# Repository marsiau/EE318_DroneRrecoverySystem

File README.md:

# EE318_DroneRrecoverySystem
Drone recovery system project for EE318

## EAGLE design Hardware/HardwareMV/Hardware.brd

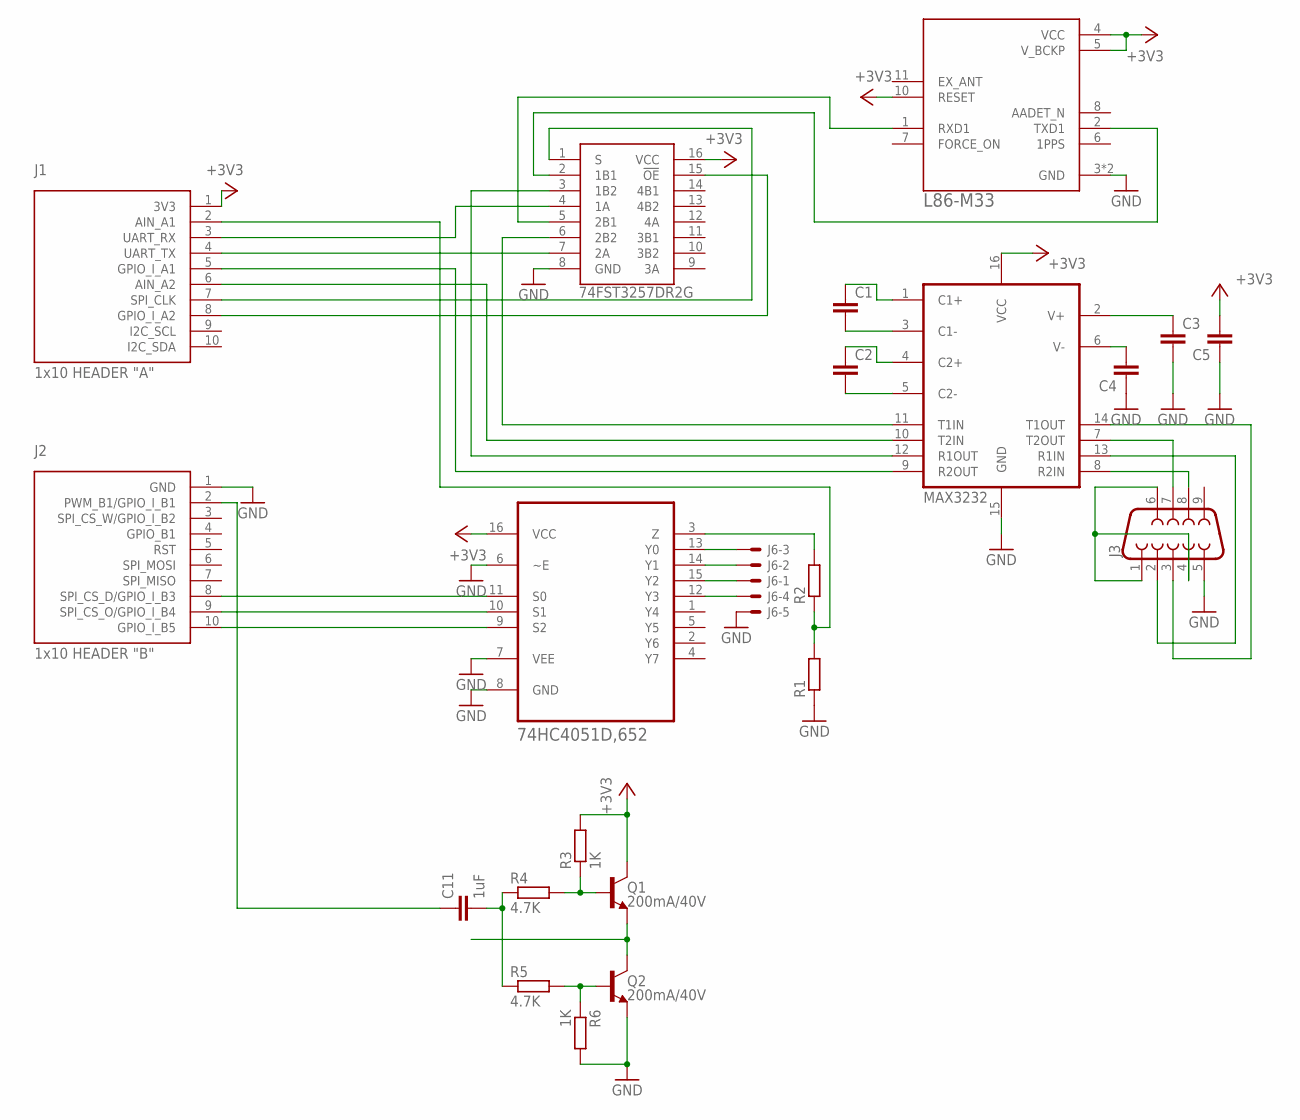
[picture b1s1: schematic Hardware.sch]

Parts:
C1, C2, C3, C4, C5: C-EUC0805K; C0805K
C11: 1uF; C025-024X044
IC1: 74FST3257DR2G; SOIC127P600X175-16N
J1: 1x10 HEADER "A"; 1X10
J2: 1x10 HEADER "B"; 1X10
J3: DB9MALE; DB9_MALE
J6: 22-27-2051-05; 6410-05
Q1, Q2: 200mA/40V; TO-92
R1, R2: R-EU_0207/7; 0207/7
R3, R6: 1K; 0207/2V
R4, R5: 4.7K; 0207/2V
U1: MAX3232; SO16
U2: L86-M33; SON254P1840X1840X40-12N
U4: 74HC4051D,652; SOIC127P600X175-16N

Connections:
+3V3: C5.2, IC1.16 (VCC), J1.1 (3V3), Q1.3 (C), R3.2, U1.16 (VCC), U2.4 (VCC), U2.5 (V_BCKP), U2.10 (RESET), U4.16 (VCC)
GND: C3.2, C4.1, C5.1, IC1.8 (GND), J2.1 (GND), J3.5, J6.5, Q2.1 (E), R1.1, R6.2, U1.15 (GND), U2.3 (GND), U2.12 (GND), U4.6 (~E), U4.7 (VEE), U4.8 (GND)
unnamed: C1.1, U1.1 (C1+)
unnamed: C1.2, U1.3 (C1-)
unnamed: IC1.4 (1A), J1.3 (UART_RX)
unnamed: C2.1, U1.4 (C2+)
unnamed: IC1.7 (2A), J1.4 (UART_TX)
unnamed: C3.1, U1.2 (V+)
unnamed: C4.2, U1.6 (V-)
unnamed: IC1.2 (1B1), U2.2 (TXD1)
unnamed: C2.2, U1.5 (C2-)
unnamed: IC1.5 (2B1), U2.1 (RXD1)
unnamed: IC1.3 (1B2), U1.12 (R1OUT)
unnamed: J3.1, J3.4, J3.6
unnamed: J3.2, U1.13 (R1IN)
unnamed: J3.3, U1.14 (T1OUT)
unnamed: J3.8, U1.8 (R2IN)
unnamed: J3.7, U1.7 (T2OUT)
unnamed: IC1.6 (2B2), U1.11 (T1IN)
unnamed: IC1.1 (S), J1.7 (SPI_CLK)
unnamed: IC1.15 (!OE), J1.8 (GPIO_I_A2)
unnamed: J6.3, U4.13 (Y0)
unnamed: J1.6 (AIN_A2), U1.10 (T2IN)
unnamed: J6.2, U4.14 (Y1)
unnamed: J6.1, U4.15 (Y2)
unnamed: J6.4, U4.12 (Y3)
unnamed: R2.2, U4.3 (Z)
unnamed: J1.5 (GPIO_I_A1), U1.9 (R2OUT)
unnamed: J1.2 (AIN_A1), R1.2, R2.1
unnamed: J2.8 (SPI_CS_D/GPIO_I_B3), U4.11 (S0)
unnamed: J2.9 (SPI_CS_O/GPIO_I_B4), U4.10 (S1)
unnamed: J2.10 (GPIO_I_B5), U4.9 (S2)
unnamed: C11.2, R4.1, R5.1
unnamed: C11.1, J2.2 (PWM_B1/GPIO_I_B1)
unnamed: Q2.2 (B), R5.2, R6.1
unnamed: Q1.2 (B), R3.1, R4.2
unnamed: Q1.1 (E), Q2.3 (C)

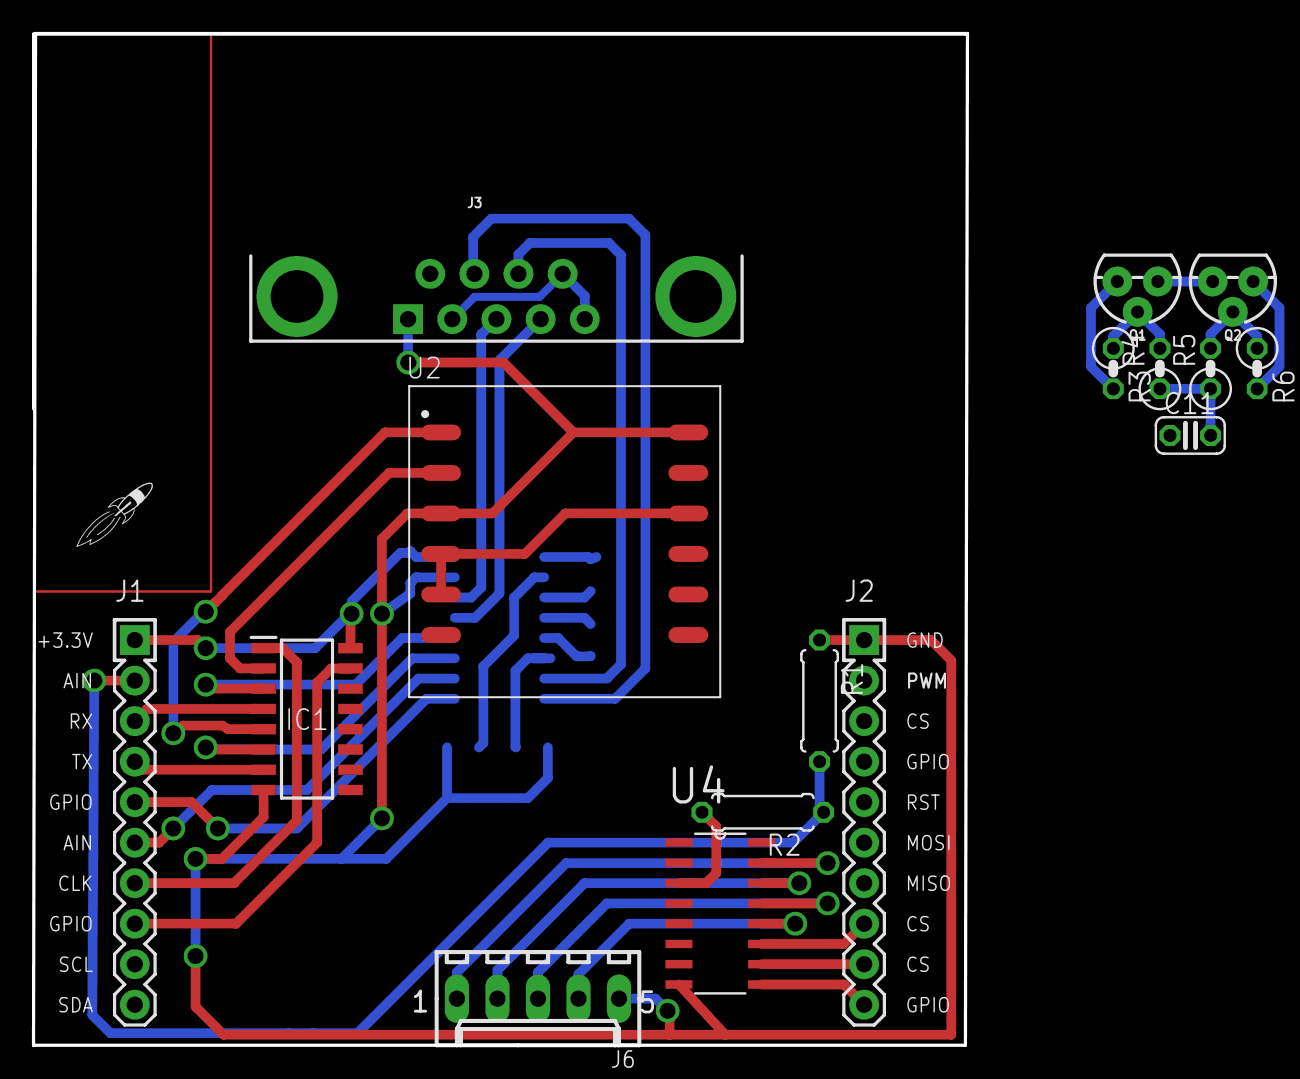
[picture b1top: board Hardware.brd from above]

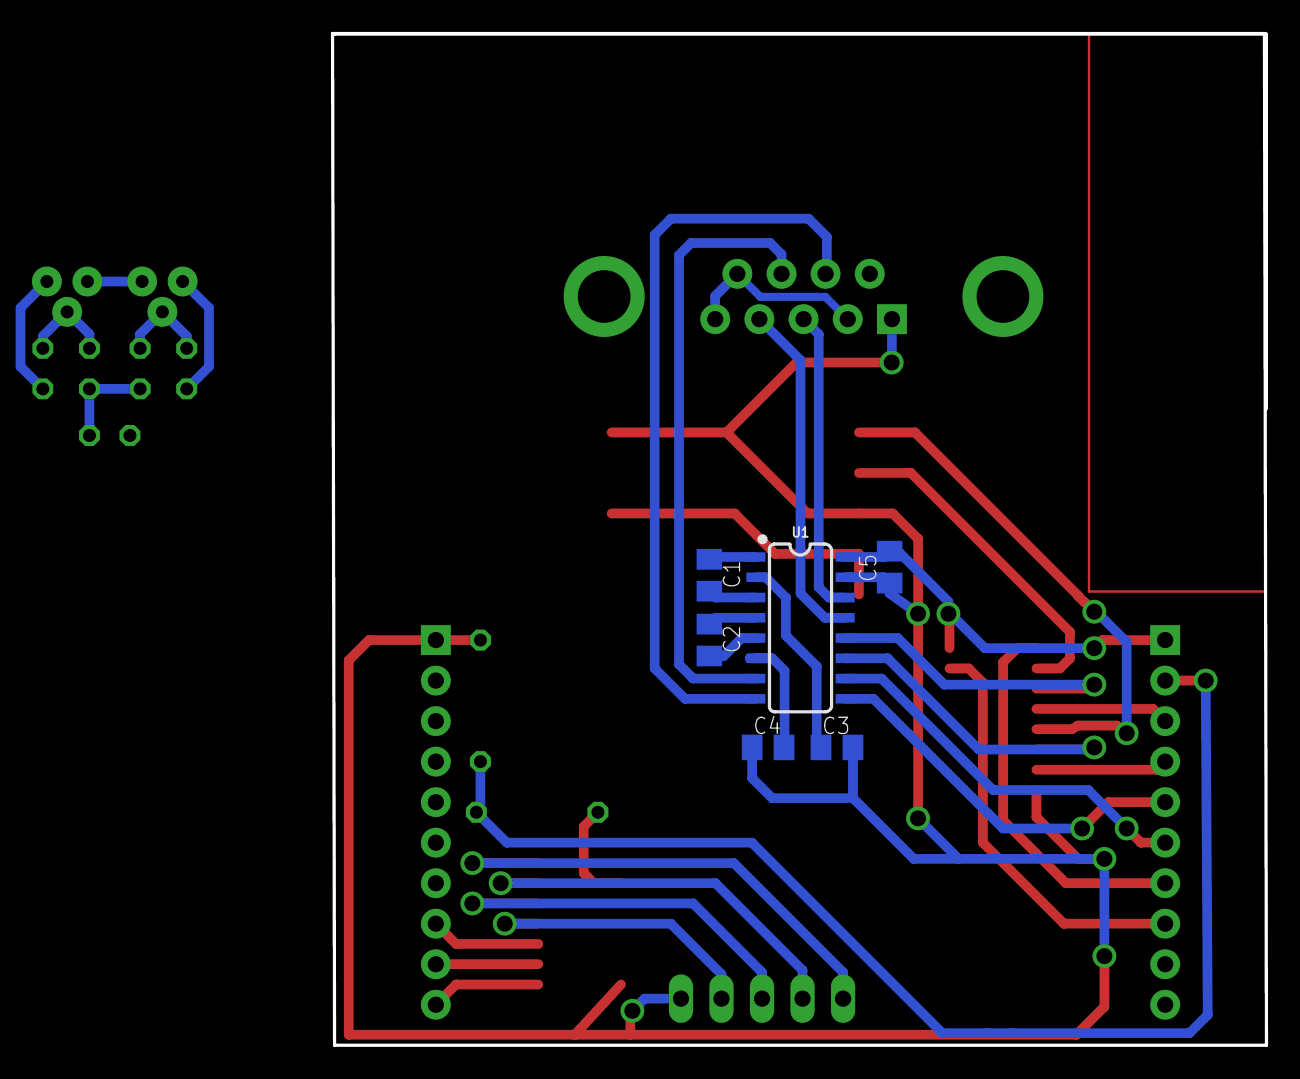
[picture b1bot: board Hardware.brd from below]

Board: 2 copper layers, 58.5 x 63.4 mm, 26 parts (7 on the bottom side), 37 nets.

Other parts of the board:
U$1: LOGO-ROCKET
U$2, U$3, U$4: METRIC_15

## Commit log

2018-02-27 Cleaning
2018-02-27 updated the .gitignore file
2018-02-27 Initial UART code commit
2018-02-28 changed RTS/CTS to active low, WORKING!
2018-02-28 Fixed the CTS line check when sending data
2018-02-28 NOT TESTED! Added received msg detection using timer A1
2018-02-28 Added Eagle files to .gitignore
2018-02-28 First hardware commit
2018-03-01 NOT TESTED! Changed RTS pin P2.5 to P8.0
2018-03-02 Fixed timer interrupt, TESTED
2018-03-02 Fixing .README
2018-03-06 test
2018-03-07 Added debouncing and general cleanup
2018-03-08 Changed pointers to arrays, found strstr() function for searching in strings, tested, working, but dodgy
2018-03-10 Increased debounce time, TESTED, strating to define commands
2018-03-14 Added libraries for GPS module and multiplexer
2018-03-14 Wrote function parsing + added FRAM persistent memory
2018-03-15 Added reference docs
2018-03-15 Added L86 files
2018-03-20 Fixed Rx data not being cleared
2018-03-22 Merged the circuit diagrams
2018-03-24 Merged and tidied up the circuit, did my part of PCB
2018-03-31 Added alternative hardware layout files
2018-03-31 minor layout changes
2018-04-03 backup
2018-04-04 Fixed msg end detection, moved on to polling display msgs, introduced low power mode
2018-04-05 Fixed Rx and msg parsing, TESTED - WORKING
2018-04-09 Changes in brd
2018-04-14 Added UART MUX support
2018-04-16 Changed to timer0, not tested, should work!
2018-04-24 Main setup for GPS test
2018-04-25 Added SMS receiving
2018-04-25 Created external file with polled msg variable for access from other subsystems, TESTED - WORKING
2018-04-25 Tri paloski
2018-04-25 Sending SMS works gdamaaamamam
2018-04-26 SMS send/receive working
2018-04-26 Added GPS parsing, not sure if working can't get lock
2018-04-26 initial merge commit
2018-04-26 current state of things
2018-04-26 Added V threshold detection
2019-02-16 Updated repo to match local versions
2019-02-16 Updated hardware to match local versions

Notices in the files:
parts and their libraries:
SparkFun-IC-Comms: Licensing: Creative Commons ShareAlike 4.0 International - https://creativecommons.org/licenses/by-sa/4.0
ruler: BSD licence
© 2012 Janusz Kostorz (janusz.kostorz@gmail.com)
All rights reserved.
End of BSD licence
